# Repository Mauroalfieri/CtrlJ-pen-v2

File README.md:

# CtrlJ-pen-v2
The CtrlJ pen is a tool that can automatically control a syringe and fluid such as solder-past, for smd components, or silicone.

More info about this project on my Blog: [mauroalfieri.it](https://mauroalfieri.it)

### 3D parts designed
CtrlJ pen v2 3D parts is made with Fusion 360:

The main changes concern the motor and pcb case, that in this version are integrated into the pen itself.

The syringe holder is the main part of the project:

with it sizes is L=142,5mm H=16,25mm P=18mm.

The other two 3D parts are the motor connector and the plunger pad to push the syringe plunger:

### PCB and schema
The electronic schema designed with Eagle software is tha following:

nn Eagle, you can place electronic components in specific coordinates and generate a PCB:

to be inserted in the 3D printed case.

### The printed case
The case designed with Fusion 360 has been printed using my Prusa i3 and PLA+ filament, the result is as follows:

and the two components:

the syringe plunger thrust system
the connector between the motor and the syringe.

were printed with a blue filament for aesthetical reasons only:

This project is released as is, without responsibility and is a DIY project under continuous development.

If you are interested you can leave a comment or contact me on the blog: [mauroalfieri.it](https://mauroalfieri.it)

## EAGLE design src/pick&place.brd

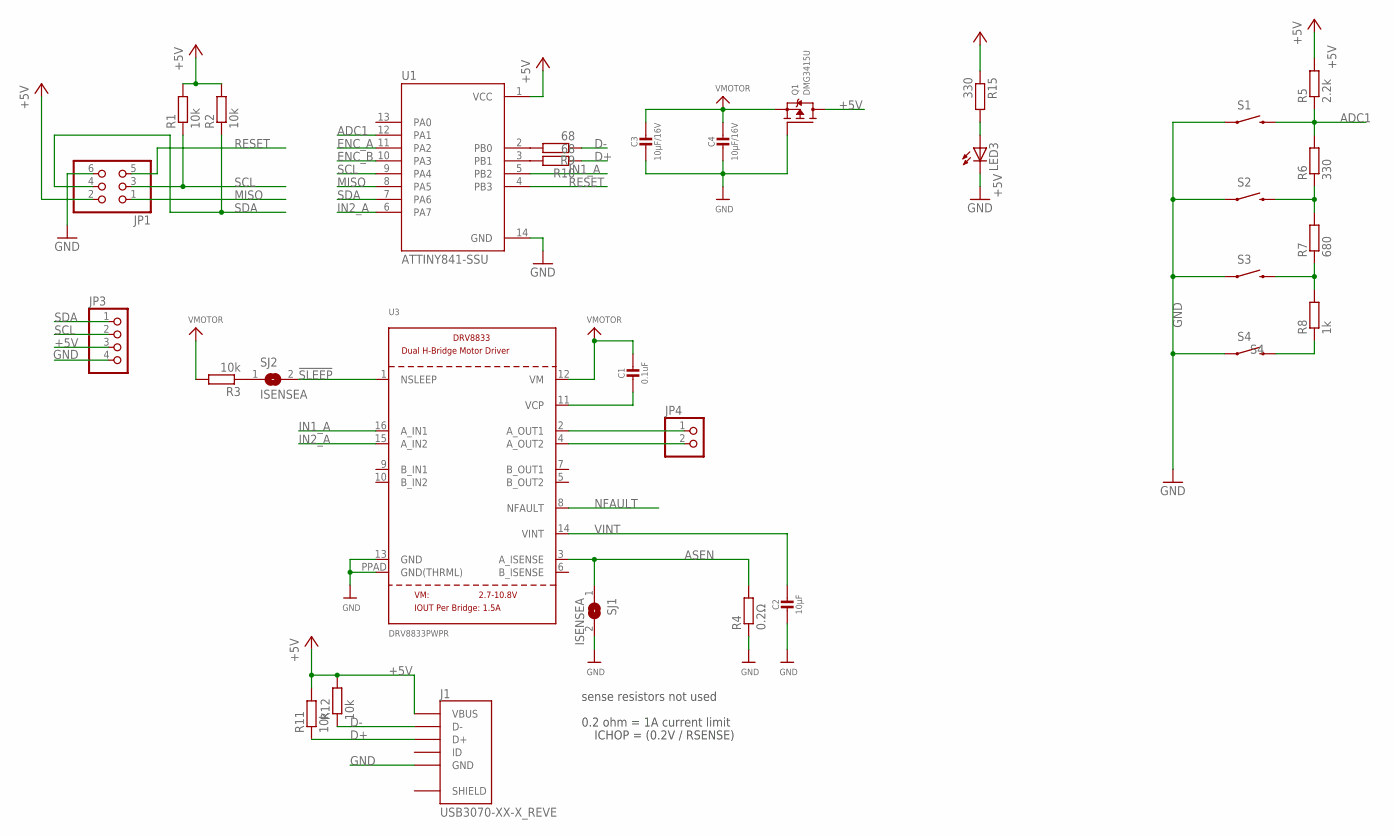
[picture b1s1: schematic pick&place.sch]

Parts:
C1: 0.1uF; 0805-NO
C2: 10µF; 0805-NO
C3, C4: 10µF/16V; 0805-NO
J1: USB3070-XX-X_REVE; GCT_USB3070-XX-X_REVE
JP1: PINHD-2X3; 2X03
JP3: HEADER-1X4ROUND; 1X04_ROUND
JP4: HEADER-1X2ROUND; 1X02_ROUND
LED3: LEDSML0805; SML0805
Q1: DMG3415U; SOT23-WIDE
R1, R2, R3, R11, R12: 10k; R0805
R4: 0.2Ω; R0805
R5: 2.2k; R0805
R6, R15: 330; R0805
R7: 680; R0805
R8: 1k; R0805
R9, R10: 68; R0805
S1: Forward; TACTILE-SWITCH-1101NE
S2: Backward; TACTILE-SWITCH-1101NE
S3: Config; TACTILE-SWITCH-1101NE
S4: SWITCH-MOMENTARY-2-SMD-1101NE; TACTILE-SWITCH-1101NE
SJ1, SJ2: ISENSEA; SOLDERJUMPER_ARROW_NOPASTE
U1: ATTINY841-SSU; SOIC127P599X175-14N
U3: DRV8833PWPR; HTSSOP16

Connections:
!SLEEP: SJ2.2, U3.1 (NSLEEP)
+5V: J1.1 (VBUS), JP1.2, JP3.3, Q1.3 (D), R1.2, R2.2, R5.2, R11.2, R12.2, R15.1, U1.1 (VCC)
ADC1: R5.1, R6.2, S1.P$2 (2), U1.12 (PA1)
AOUT1: JP4.1, U3.2 (A_OUT1)
AOUT2: JP4.2, U3.4 (A_OUT2)
ASEN: R4.2, SJ1.1, U3.3 (A_ISENSE)
D+: J1.3 (D+), R10.1, R11.1
D-: J1.2 (D-), R9.1, R12.1
ENC_A: U1.11 (PA2)
ENC_B: U1.10 (PA3)
GND: C2.2, C3.2, C4.2, J1.5 (GND), JP1.6, JP3.4, LED3.C, Q1.1 (G), R4.1, S1.P$1 (1), S2.P$1 (1), S3.P$1 (1), S4.P$1 (1), SJ1.2, U1.14 (GND), U3.13 (GND), U3.PPAD (GND(THRML))
IN1_A: U1.5 (PB2), U3.16 (A_IN1)
IN2_A: U1.6 (PA7), U3.15 (A_IN2)
MISO: JP1.1, U1.8 (PA5)
unnamed: R3.1, SJ2.1
unnamed: R9.2, U1.2 (PB0)
unnamed: R10.2, U1.3 (PB1)
unnamed: C1.2, U3.11 (VCP)
unnamed: R7.1, R8.2, S3.P$2 (2)
unnamed: LED3.A, R15.2
unnamed: R6.1, R7.2, S2.P$2 (2)
NFAULT: U3.8 (NFAULT)
RESET: JP1.5, U1.4 (PB3)
S4: R8.1, S4.P$2 (2)
SCL: JP1.3, JP3.2, R1.1, U1.9 (PA4)
SDA: JP1.4, JP3.1, R2.1, U1.7 (PA6)
SHIELD: J1.6 (SHIELD), J1.7 (SHIELD)
VINT: C2.1, U3.14 (VINT)
VMOTOR: C1.1, C3.1, C4.1, Q1.2 (S), R3.2, U3.12 (VM)

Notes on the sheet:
sense resistors not used
0.2 ohm = 1A current limit
ICHOP = (0.2V / RSENSE)

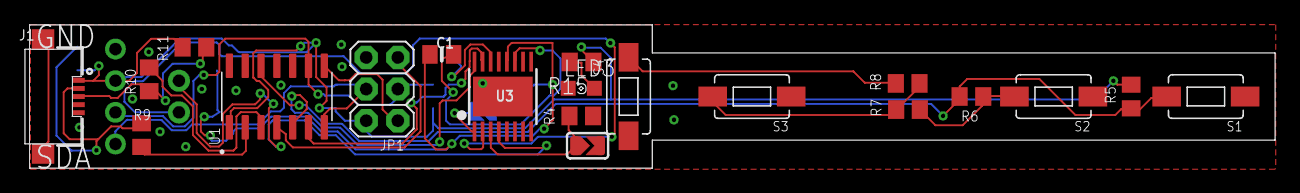
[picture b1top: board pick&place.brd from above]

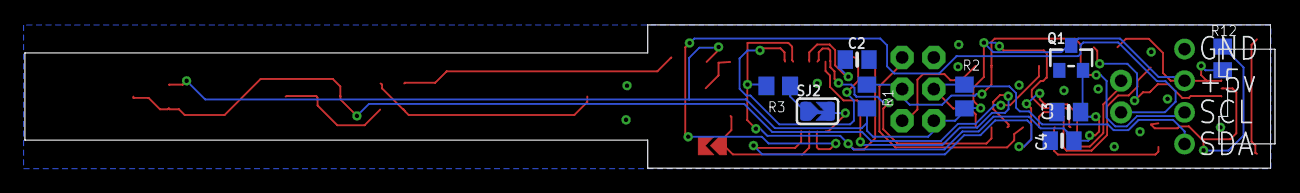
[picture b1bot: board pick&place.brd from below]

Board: 2 copper layers, 100.0 x 11.5 mm, 31 parts (9 on the bottom side), 26 nets.

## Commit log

2022-02-04 First Upload
2022-02-05 folder src renamed in eagle
2022-02-05 removed duplicate images
2022-02-05 Writed the first draft of README file
2022-02-06 Images Added
2022-02-24 added stl file

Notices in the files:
parts and their libraries:
SparkFun: Licensing: CC v3.0 Share-Alike You are welcome to use this library for commercial purposes.
microbuilder: This work is placed in the public domain, and may be freely used for commercial and non-commercial work with the following conditions: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
